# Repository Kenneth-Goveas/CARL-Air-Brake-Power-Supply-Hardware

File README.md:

# CARL Air Brake Power Supply Hardware

This repository contains the electronic hardware design for the power supply
module of the [CARL Air Brake][cab-repo] computer. The CARL Air Brake computer
automatically controls a rocket air brake in flight, so that the vehicle attains
an apogee at the desired altitude. Its power supply module distributes
electrical power to all systems in the computer.

![Top view of the power supply module](
  ./documentation/images/top_view.png
)

![Bottom view of the power supply module](
  ./documentation/images/bottom_view.png
)

Detailed documentation for this repository can be found in the following files.

- [description.md][des]:
  Detailed description of the power supply module.
- [cloning.md][cln]:
  Properly cloning this repository along with all its submodules.
- [prerequisites.md][req]:
  Necessary software for viewing and editing the electronic design.
- [organization.md][org]:
  Directory structure and organization of files in this repository.
- [flashing.md][fsh]:
  Flashing software onto the power supply module.

[des]:      ./documentation/description.md
[cln]:      ./documentation/cloning.md
[req]:      ./documentation/prerequisites.md
[org]:      ./documentation/organization.md
[fsh]:      ./documentation/flashing.md

[cab-repo]: https://github.com/Kenneth-Goveas/CARL-Air-Brake

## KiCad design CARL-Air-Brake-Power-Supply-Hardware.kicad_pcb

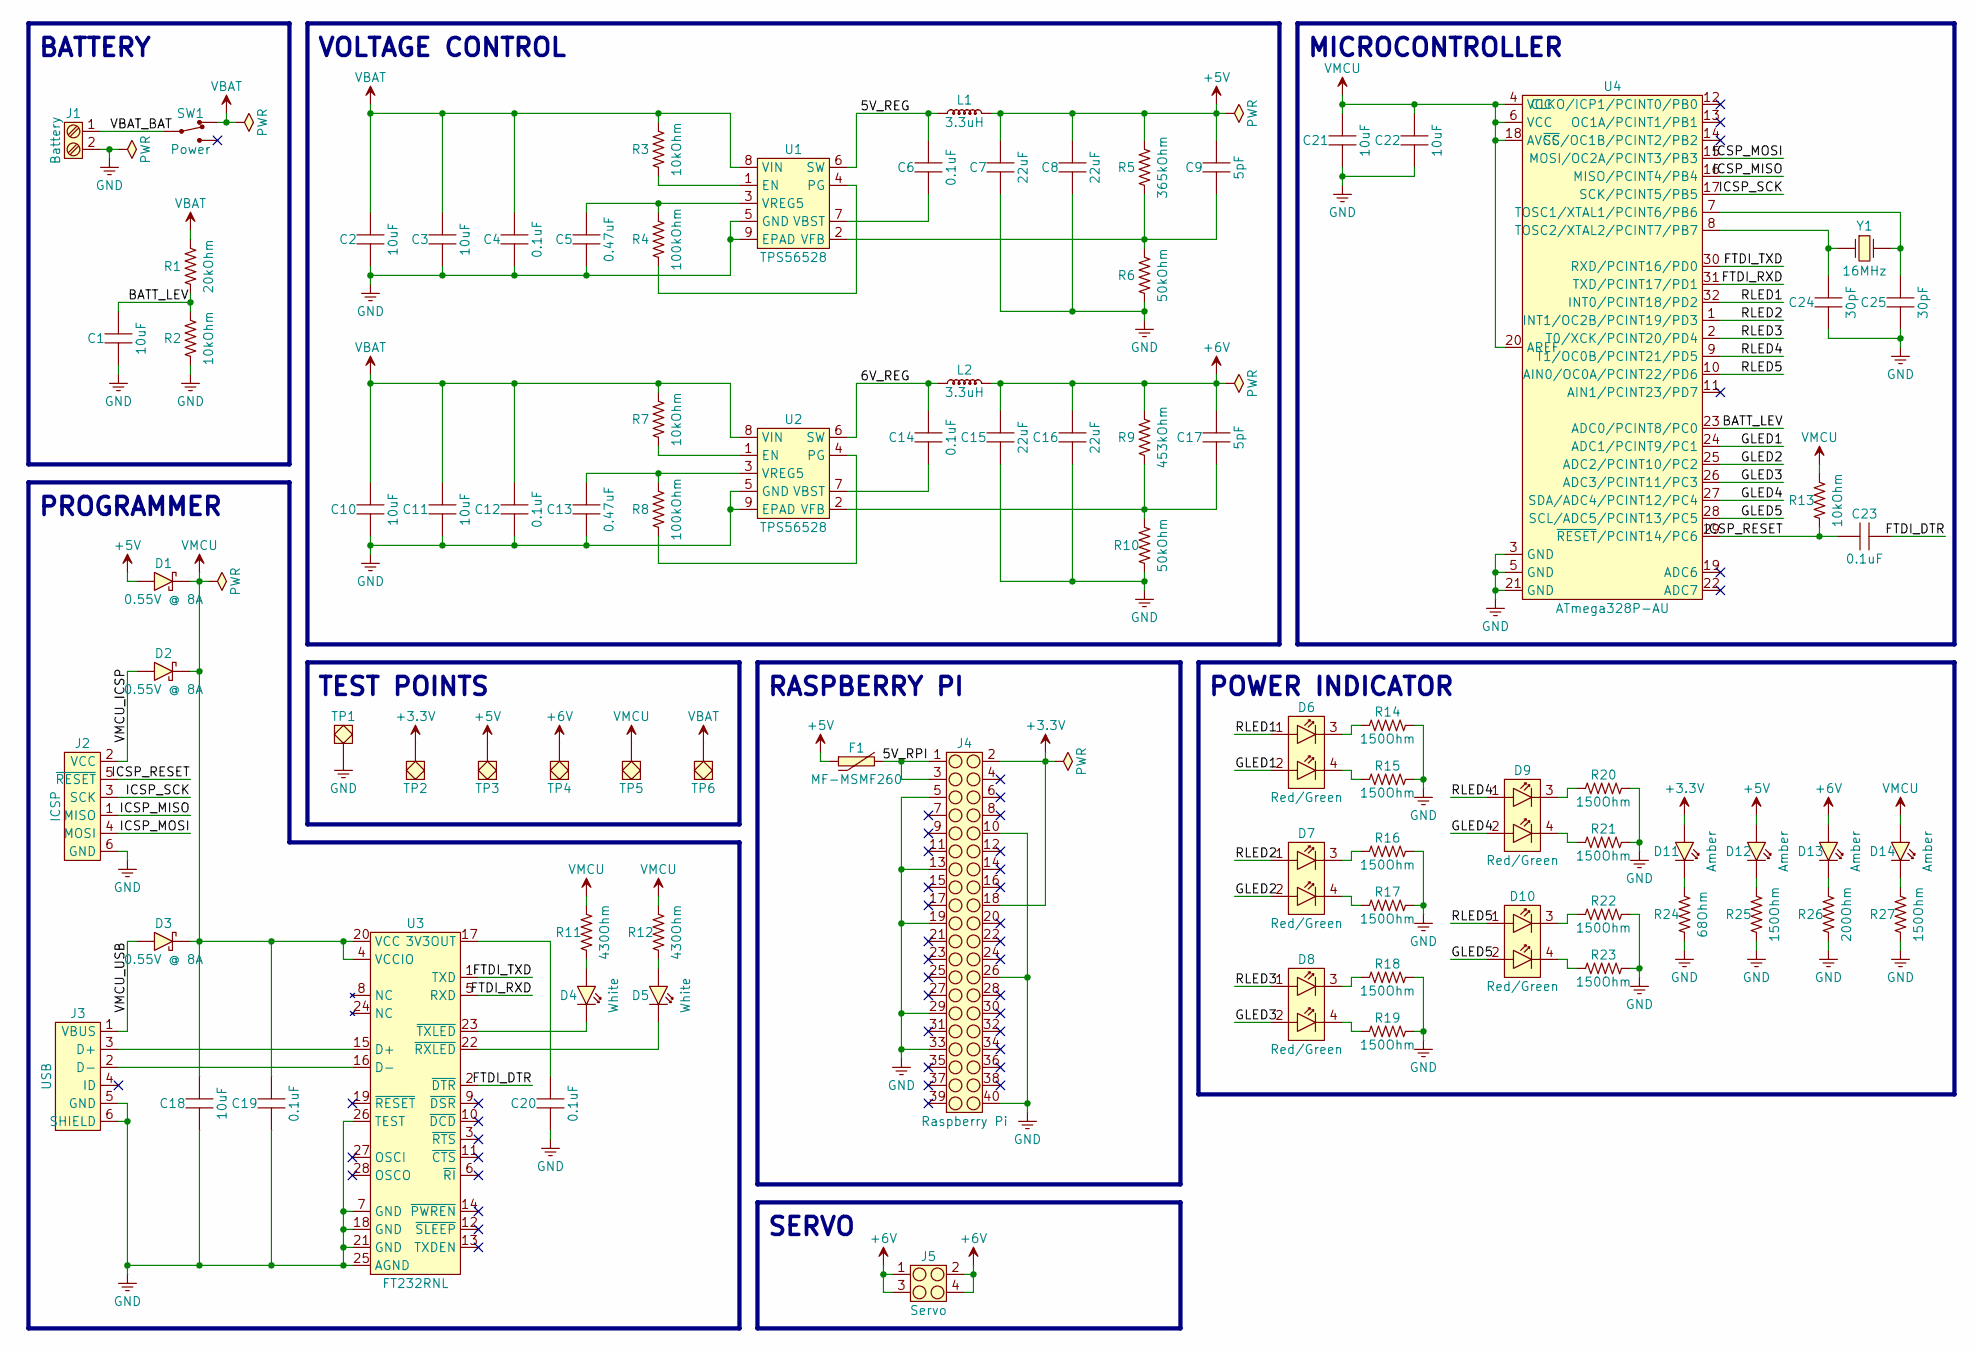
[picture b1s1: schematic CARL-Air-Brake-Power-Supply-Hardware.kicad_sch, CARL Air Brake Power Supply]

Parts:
C1, C2, C3, C10, C11, C18, C21, C22: 10uF; Cap_Ceramic_0603
C4, C6, C12, C14, C19, C20, C23: 0.1uF; Cap_Ceramic_0603
C5, C13: 0.47uF; Cap_Ceramic_0603
C7, C8, C15, C16: 22uF; Cap_Ceramic_0603
C9, C17: 5pF; Cap_Ceramic_0603
C24, C25: 30pF; Cap_Ceramic_0603
D1, D2, D3: 0.55V @ 8A; Diode_DO-214AB_SMC
D4, D5: White; LED_0603
D6, D7, D8, D9, D10: Red/Green; LED_Dual_Wuerth_WL-SBTW
D11, D12, D13, D14: Amber; LED_0603
F1: MF-MSMF260; Fuse_PTC_1812
J1: Battery; ScrewTerm_02_CUI_TB003-500-02BK
J2: ICSP; PinHead_02x03_Pitch2.54mm_Bot3.00mm_Top6.00mm_Shroud2.50mm
J3: USB; USB_Micro_B_Recp_Wuerth_629105136821
J4: Raspberry Pi; StackHead_02x20_Pitch2.54mm_Bot10.50mm_Top8.50mm
J5: Servo; PinHead_02x02_Pitch2.54mm_Bot3.00mm_Top6.00mm_Shroud2.50mm
L1, L2: 3.3uH; Ind_Eaton_DR127
R1: 20kOhm; Res_Film_0603
R2, R3, R7, R13: 10kOhm; Res_Film_0603
R4, R8: 100kOhm; Res_Film_0603
R5: 365kOhm; Res_Film_0603
R6, R10: 50kOhm; Res_Film_0603
R9: 453kOhm; Res_Film_0603
R11, R12: 430Ohm; Res_Film_0603
R14, R15, R16, R17, R18, R19, R20, R21, R22, R23, R25, R27: 150Ohm; Res_Film_0603
R24: 68Ohm; Res_Film_0603
R26: 200Ohm; Res_Film_0603
SW1: Power; Switch_SPDT_Salecom_T80-S-TS-13P-A1-2-R
TP1, TP2, TP3, TP4, TP5, TP6: TestPoint_CircPad2.00mm_CircMsk2.50mm
U1, U2: TPS56528; SOIC_08_Dim4.00x5.00x1.70mm_Pitch1.27mm_RectThPad2.95x4.90m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
U3: FT232RNL; SOIC_28_Dim5.50x10.50x2.00mm_Pitch0.65mm
U4: ATmega328P-AU; TQFP_08x08_Dim7.00x7.00x1.20mm_Pitch0.80mm
Y1: 16MHz; Crystal_HC49-US

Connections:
/5V_REG: C6.2, L1.1, U1.6 (SW)
/5V_RPI: F1.2, J4.1, J4.3
/6V_REG: C14.2, L2.1, U2.6 (SW)
/BATT_LEV: C1.2, R1.1, R2.2, U4.23 (ADC0/PCINT8/PC0)
/FTDI_DTR: C23.2, U3.2 (~DTR)
/FTDI_RXD: U3.5 (RXD), U4.31 (TXD/PCINT17/PD1)
/FTDI_TXD: U3.1 (TXD), U4.30 (RXD/PCINT16/PD0)
/GLED1: D6.2 (A), U4.24 (ADC1/PCINT9/PC1)
/GLED2: D7.2 (A), U4.25 (ADC2/PCINT10/PC2)
/GLED3: D8.2 (A), U4.26 (ADC3/PCINT11/PC3)
/GLED4: D9.2 (A), U4.27 (SDA/ADC4/PCINT12/PC4)
/GLED5: D10.2 (A), U4.28 (SCL/ADC5/PCINT13/PC5)
/ICSP_MISO: J2.1 (MISO), U4.16 (MISO/PCINT4/PB4)
/ICSP_MOSI: J2.4 (MOSI), U4.15 (MOSI/OC2A/PCINT3/PB3)
/ICSP_RESET: C23.1, J2.5 (~RESET), R13.1, U4.29 (~RESET/PCINT14/PC6)
/ICSP_SCK: J2.3 (SCK), U4.17 (SCK/PCINT5/PB5)
/RLED1: D6.1 (A), U4.32 (INT0/PCINT18/PD2)
/RLED2: D7.1 (A), U4.1 (INT1/OC2B/PCINT19/PD3)
/RLED3: D8.1 (A), U4.2 (T0/XCK/PCINT20/PD4)
/RLED4: D9.1 (A), U4.9 (T1/OC0B/PCINT21/PD5)
/RLED5: D10.1 (A), U4.10 (AIN0/OC0A/PCINT22/PD6)
/VBAT_BAT: J1.1, SW1.2
/VMCU_ICSP: D2.1 (A), J2.2 (VCC)
/VMCU_USB: D3.1 (A), J3.1 (VBUS)
unnamed: D4.1 (A), R11.1
unnamed: D4.2 (K), U3.23 (~TXLED)
unnamed: D5.1 (A), R12.1
unnamed: D5.2 (K), U3.22 (~RXLED)
unnamed: D6.3 (K), R14.1
unnamed: D6.4 (K), R15.1
unnamed: D7.3 (K), R16.1
unnamed: D7.4 (K), R17.1
unnamed: D8.3 (K), R18.1
unnamed: D8.4 (K), R19.1
unnamed: D9.3 (K), R20.1
unnamed: D9.4 (K), R21.1
unnamed: D10.3 (K), R22.1
unnamed: D10.4 (K), R23.1
unnamed: D11.2 (K), R24.2
unnamed: D12.2 (K), R25.2
unnamed: D13.2 (K), R26.2
unnamed: D14.2 (K), R27.2
unnamed: J3.3 (D+), U3.15 (D+)
unnamed: J3.2 (D-), U3.16 (D-)
unnamed: R3.1, U1.1 (EN)
unnamed: R4.1, U1.4 (PG)
unnamed: C6.1, U1.7 (VBST)
unnamed: C9.1, R5.1, R6.2, U1.2 (VFB)
unnamed: C5.2, R4.2, U1.3 (VREG5)
unnamed: R7.1, U2.1 (EN)
unnamed: R8.1, U2.4 (PG)
unnamed: C14.1, U2.7 (VBST)
unnamed: C17.1, R9.1, R10.2, U2.2 (VFB)
unnamed: C13.2, R8.2, U2.3 (VREG5)
unnamed: C20.2, U3.17 (3V3OUT)
unnamed: C25.2, U4.7 (TOSC1/XTAL1/PCINT6/PB6), Y1.2
unnamed: C24.2, U4.8 (TOSC2/XTAL2/PCINT7/PB7), Y1.1

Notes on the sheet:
BATTERY
MICROCONTROLLER
TEST POINTS
RASPBERRY PI
PROGRAMMER
POWER INDICATOR
SERVO
VOLTAGE CONTROL

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
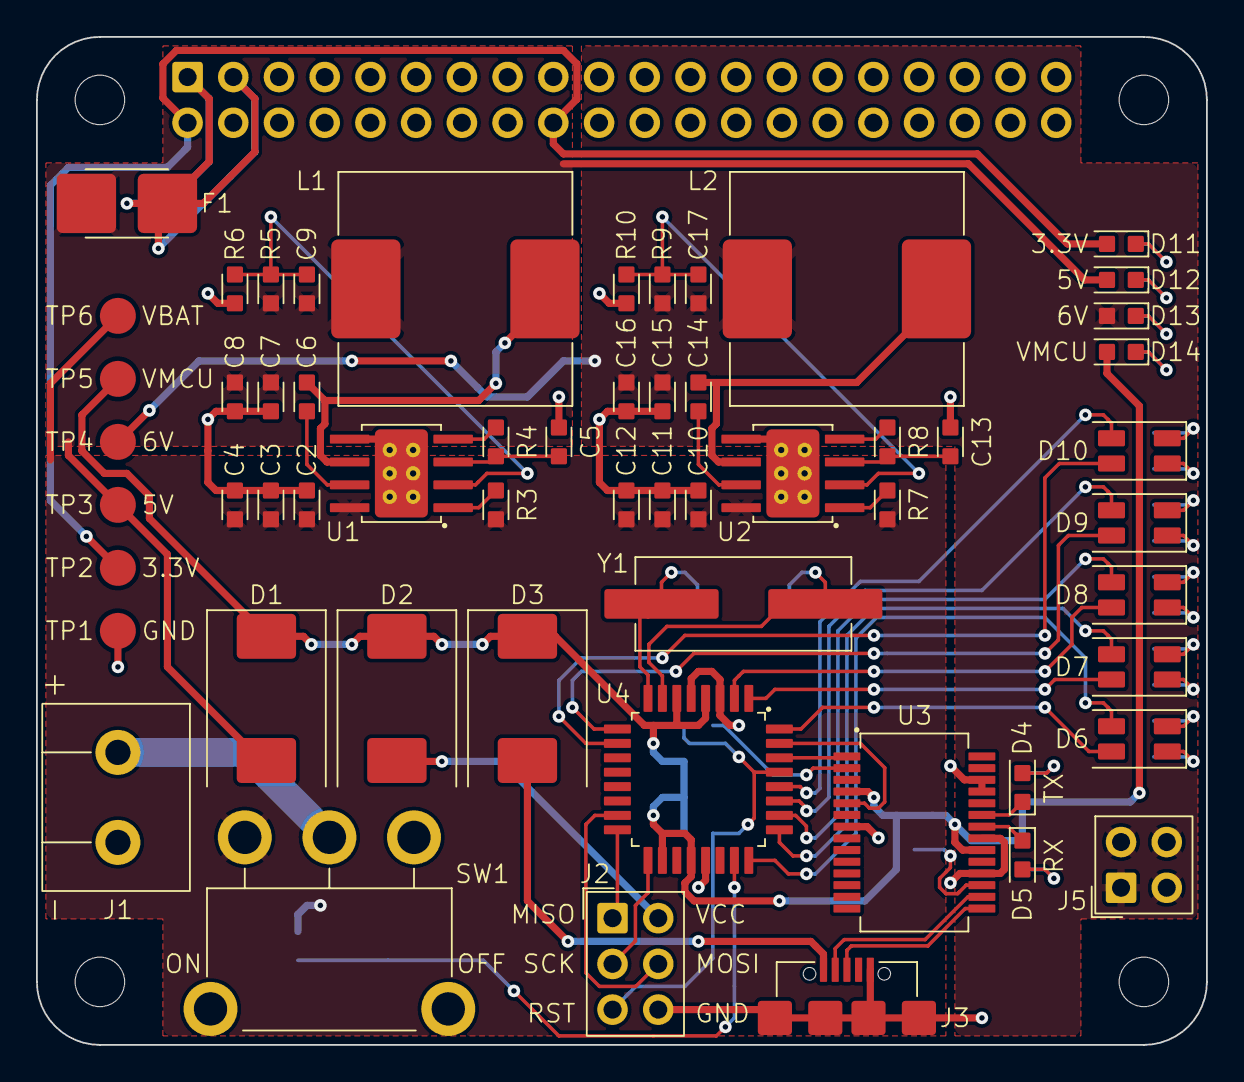
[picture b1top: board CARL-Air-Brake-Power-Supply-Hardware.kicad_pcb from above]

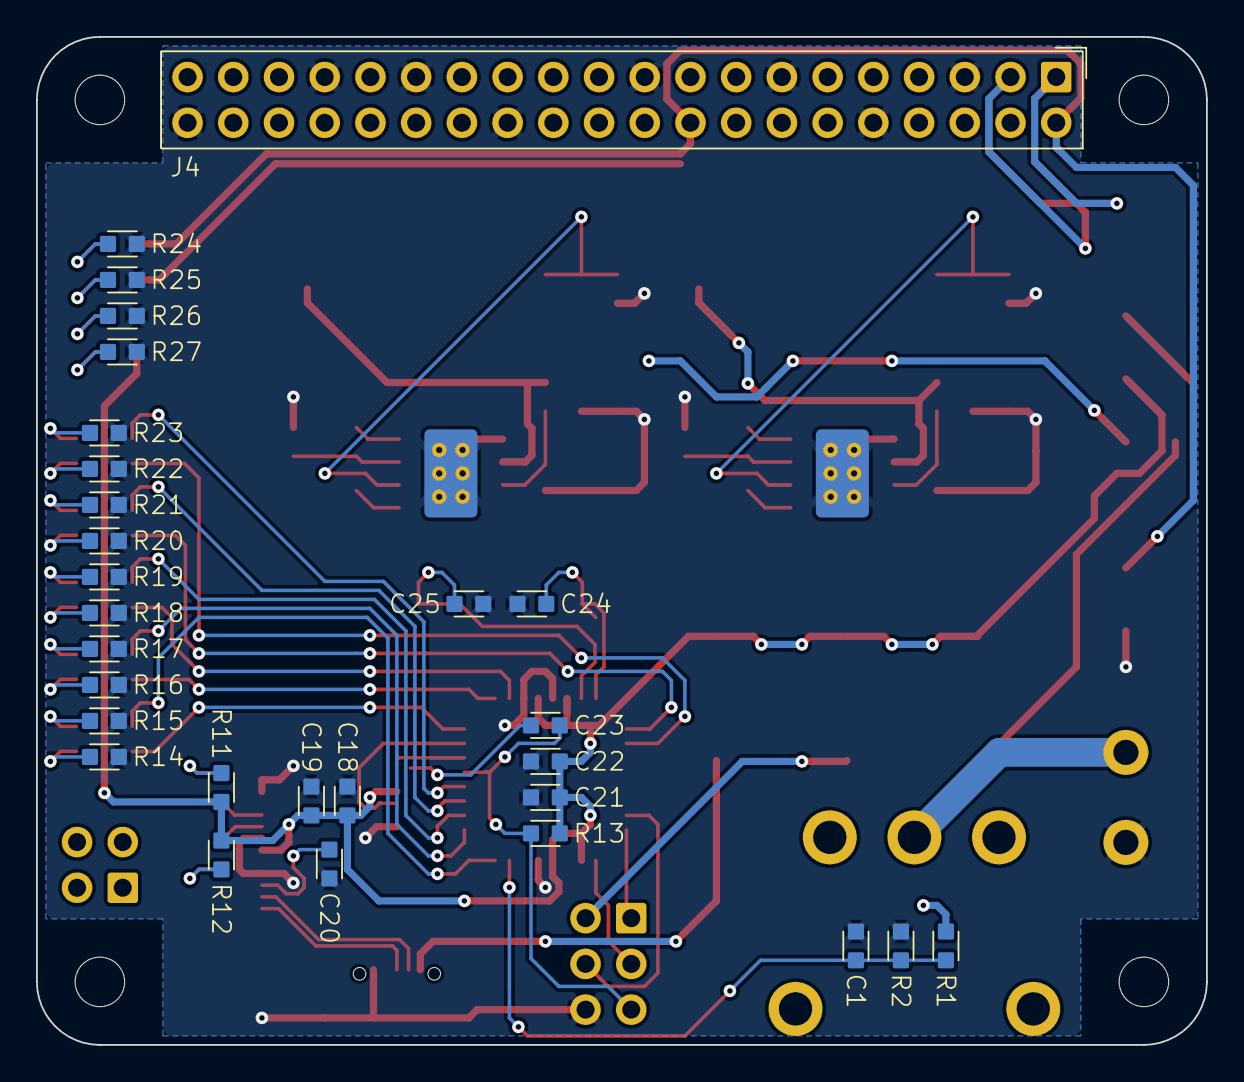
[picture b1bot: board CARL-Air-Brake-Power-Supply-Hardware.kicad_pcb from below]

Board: 2 copper layers, 65.0 x 56.0 mm, 86 parts (29 on the bottom side), 63 nets.

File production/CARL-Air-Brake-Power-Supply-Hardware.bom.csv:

Serial,Reference,Manufacturer,Part,Description,Quantity
1,R24,Yageo,AC0603FR-0768RL,Resistor 68Ohm 100mW 1% 0603,1
2,R14 R15 R16 R17 R18 R19 R20 R21 R22 R23 R25 R27,Yageo,RC0603FR-10150RL,Resistor 150Ohm 100mW 1% 0603,12
3,R26,Yageo,RC0603FR-07200RL,Resistor 200Ohm 100mW 1% 0603,1
4,R11 R12,Yageo,RT0603DRE07430RL,Resistor 430Ohm 100mW 0.5% 0603,2
5,R2 R3 R7 R13,Yageo,RT0603FRE1310KL,Resistor 10kOhm 100mW 1% 0603,4
6,R1,Yageo,RC0603FR-1320KL,Resistor 20kOhm 100mW 1% 0603,1
7,R6 R10,Yageo,RT0603BRD0750KL,Resistor 50kOhm 100mW 0.1% 0603,2
8,R4 R8,Yageo,RC0603FR-07100KL,Resistor 100kOhm 100mW 1% 0603,2
9,R5,Yageo,AC0603FR-07365KL,Resistor 365kOhm 100mW 1% 0603,1
10,R9,Yageo,RC0603FR-07453KL,Resistor 453kOhm 100mW 1% 0603,1
11,C9 C17,Murata,GRM1885C1H5R0WA01D,Capacitor 5pF 50V 1% 0603,2
12,C24 C25,Murata,GRM1885C1H300GA01D,Capacitor 30pF 50V 2% 0603,2
13,C4 C6 C12 C14 C19 C20 C23,Murata,GCM188R71C104JA37D,Capacitor 0.1uF 16V 5% 0603,7
14,C5 C13,Murata,GRM188R61A474JA61D,Capacitor 0.47uF 10V 5% 0603,2
15,C1 C2 C3 C10 C11 C18 C21 C22,Murata,GRT188R61C106KE13J,Capacitor 10uF 16V 10% 0603,8
16,C7 C8 C15 C16,Murata,GRM188R61A226ME15D,Capacitor 22uF 10V 20% 0603,4
17,L1 L2,Eaton,DR127-3R3-R,Inductor 3.3uH 10.5A (rms) 21.5A (sat) 20%,2
18,F1,Bourns,MF-MSMF260-2,Fuse PTC 2.6A (hold) 5.2A (trip) 6V 1812,1
19,D1 D2 D3,Diotec,SK84-AQ,Diode Schottky 0.55V @ 8A DO-214AB/SMC,3
20,D4 D5,Ams Osram,LW Q38G-Q1OO-3K6L-1,LED White 2.85V @ 5mA 0603,2
21,D11 D12 D13 D14,Wuerth,150060AS75000,LED Amber 2V @ 20mA 0603,4
22,D6 D7 D8 D9 D10,Wuerth,150141RV73100,LED Red Green 2V @ 20mA,5
23,Y1,ECS,ECS-160-20-5PX-TR,Crystal 16Mhz 20pF HC49-US,1
24,J2,Adam Tech,PH2-06-UA,Pin Header 2x3,1
25,J1,CUI,TB003-500-P02BE,Screw Terminal 2-Pin,1
26,J3,Wuerth,629105136821,Micro USB Receptacle,1
27,J4,Adafruit,2223,Stacking Header 2x20,1
28,J5,Wuerth,61300421121,Pin Header 2x2,1
29,SW1,Salecom,T80-S-TS-13P-A1-2-R-E-H,Switch SPDT,1
30,U1 U2,TI,TPS56528DDAR,Buck converter,2
31,U3,FTDI,FT232RNL-REEL,USB-UART Bridge,1
32,U4,Microchip,ATmega328P-AU,8-Bit AVR Microcontroller,1

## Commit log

2023-12-07 Initialized repository
    Created empty repository with .gitignore file.
2023-12-07 Added KiCad library
    Cloned KiCad component library as submodule.
2023-12-07 Initialized KiCad project
    Created KiCad project files without any circuit design.
2023-12-08 Added schematic
    Completed circuit schematic and performed ERC.
2023-12-08 Assigned footprints
    Assigned footprints to all symbols in circuit schematic.
2023-12-10 Arranged components
    Created board layout and placed components at suitable locations.
2023-12-11 Added test point for VBAT
    Added test point for VBAT line and updated PCB accordingly.
2023-12-11 Added filled zones
    Added filled copper zones for high current power supply lines.
2023-12-12 Updated library
    Pulled latest updates to component library.
2023-12-13 Routed circuit board
    Completed circuit design by routing all connections, and performed DRC.
2023-12-20 Added README
    Added README and supporting documentation.
2023-12-20 Added local settings file to gitignore
    Removed local settings file *.kicad_prl and added it to gitignore.
2023-12-20 Updated documentation
    Corrected typos in documentation and made additional minor edits.
2023-12-20 Changed VBUS to VMCU
    Changed name of VBUS net to VMCU in schematic and board files.
2023-12-20 Changed submodule URL from SSH to HTTPS
    Changed URL of component library submodule from SSH to HTTPS. This way,
    users who haven't set up SSH keys on GitHub will still be able to
    recursively clone the repository without any trouble.
2023-12-20 Corrected component values
    Corrected resistance values of resistors R6 and R10.
2023-12-21 Added bill of materials
    Created production directory and added bill of materials.
2023-12-21 Added DRC rule to flag drills inside courtyards
    Modified DRC rules to flag the presence of PTH or NPTH drills inside
    footprint courtyards as errors instead of ignoring them. Performed DRC
    after making this update.
2023-12-21 Plotted gerber and drill files
    Configured settings for gerber and drill file generation and plotted
    gerber and drill files.
2023-12-21 Renamed BOM file
    Renamed bill of materials file to match naming convention used in other
    production-related files.
2023-12-22 Added temporary files to gitignore
    Added entries in gitignore for lock files generated by KiCad and swap
    files generated by Vim.
2023-12-22 Updated documentation
    Updated documentation to include production directory in description of
    project organization.
2023-12-22 Updated documentation
    Made minor modifications to the documentation to make it more accurate.
2026-01-06 Updated documentation
    Updated images and corresponding text in documentation for better
    clarity and sync with other repositories.
